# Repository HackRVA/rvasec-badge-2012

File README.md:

RvaSec Badge 2012
=================

This repository contains all the notes, design files and documentation for the RvaSec security conference for 2012

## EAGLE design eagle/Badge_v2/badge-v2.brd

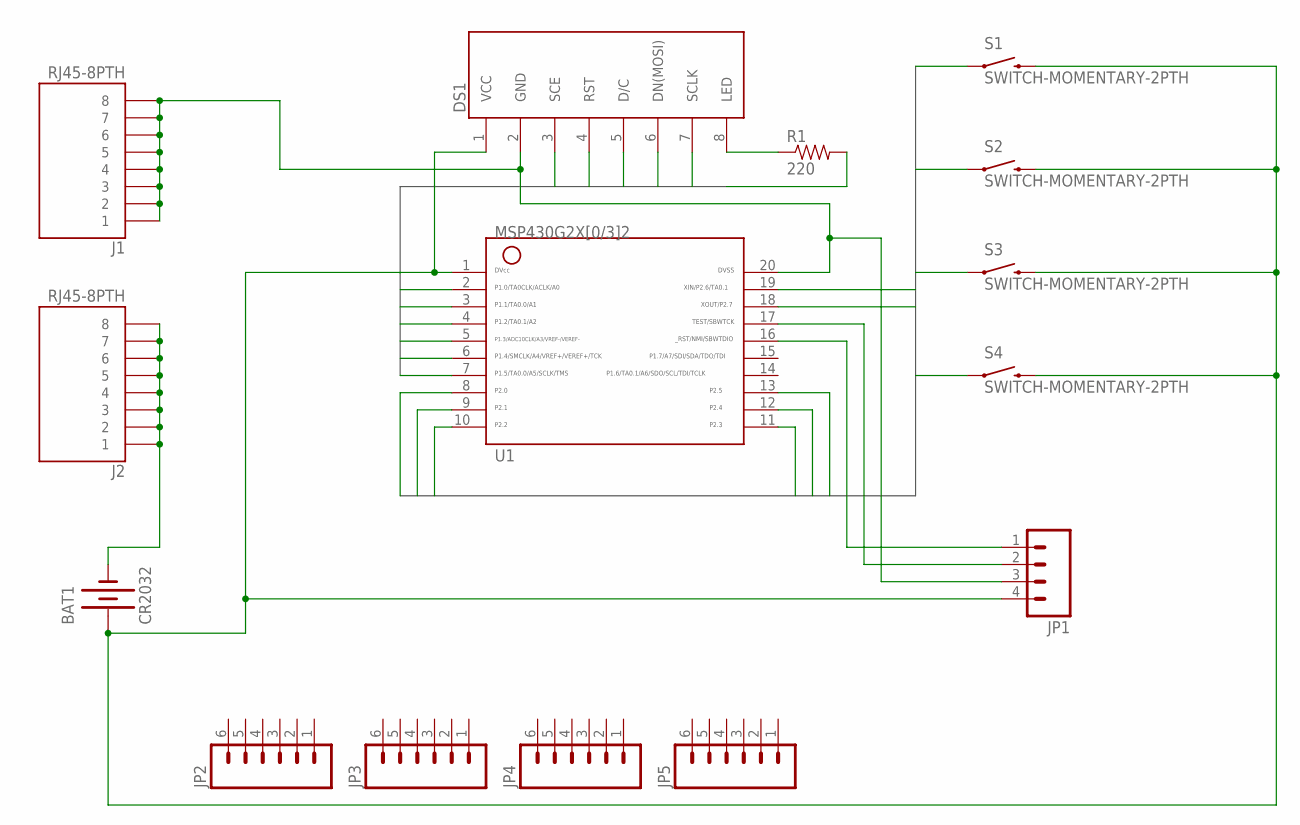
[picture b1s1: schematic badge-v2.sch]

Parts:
BAT1: CR2032; BATTCOM_20MM_4LEGS_PTH
DS1: NOK_5110_LCD; 1X08
J1, J2: RJ45-8PTH; RJ45-8
JP1: M04PTH; 1X04
JP2, JP3, JP4, JP5: M06SIP; 1X06
R1: 220; AXIAL-0.3
S1, S2, S3, S4: SWITCH-MOMENTARY-2PTH; TACTILE-PTH
U1: G2X[0/3]2---N20; N20

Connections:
unnamed: DS1.8 (LED), R1.P$1 (1)
PORTONE0: DS1.4 (RST), U1.2
PORTONE1: DS1.5 (D/C), U1.3
PORTONE2: DS1.6 (DN(MOSI)), U1.4
PORTONE3: DS1.7 (SCLK), U1.5
PORTONE4: R1.P$2 (2), U1.6
PORTONE5: DS1.3 (SCE), U1.7
PORTTWO0: S1.1, U1.8
PORTTWO1: S2.1, U1.9
PORTTWO2: S3.1, U1.10
PORTTWO3: S4.1, U1.11
PORTTWO4: U1.12
PORTTWO5: U1.13
PORTTWO6: U1.19
PORTTWO7: U1.18
RST: JP1.1, U1.16
TEST: JP1.2, U1.17
VCC: BAT1.P$POS1 (+), DS1.1 (VCC), JP1.4, S1.3 (2), S2.3 (2), S3.3 (2), S4.3 (2), U1.1
VSS1: BAT1.P$NEG (-), J2.1, J2.2, J2.3, J2.4, J2.5, J2.6, J2.7, J2.8
VSS2: DS1.2 (GND), J1.1, J1.2, J1.3, J1.4, J1.5, J1.6, J1.7, J1.8, JP1.3, U1.20

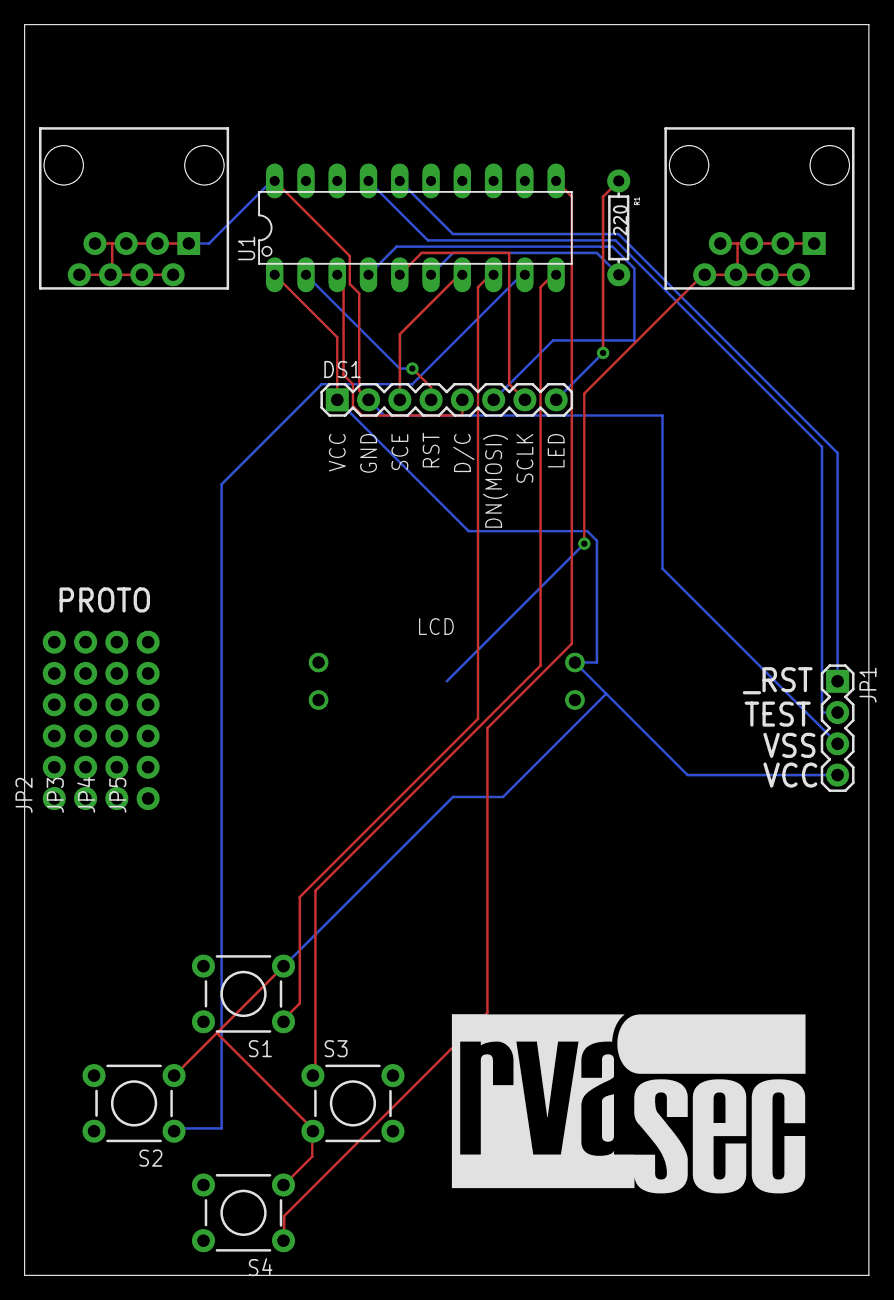
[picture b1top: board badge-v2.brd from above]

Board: 2 copper layers, 68.6 x 101.6 mm, 16 parts (1 on the bottom side), 16 nets.

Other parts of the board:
U$1: RVA_SEC_LOGO_LARGE

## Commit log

2012-05-01 Added initial documentation and readme
    * Added lcd datasheet
    * Added all files to replicate my eagle session
2012-05-01 Project layout changes
    * Added empty eagle project directory
    * Moved files for setting up eagle environment to eagle/env
2012-05-02 Added graphics in various formats
    * Converted graphic to data array compatible with Nokia 5510
2012-05-02 Added MSP430 part library
    * Added schematic file with microcontroller
2012-05-03 Added rough logo display sketch
2012-05-03 Updated image and graphics data array
    * Removed wasted space around edge of image
    * Removed original eagle part libary for MSP430 (renamed)
2012-05-05 Added a second image
    * Modified pins to map to arduino pro mini
2012-06-15 Graphics!
    * Added all final graphics
2012-06-15 Documentation
    Added pdf for rj45 connector
2012-06-15 Added final eagle files
    * NOTE - I have modified some parts from the standard sparkfun library, I
    don't remember all of which. Be warned of my unorganized nature.
2012-06-15 Added custom parts
    * Added the library of parts that weren't in the sparkfun library or
    elsewhere
2012-06-15 Added source files
    * Don't peek at all the goodies before the conference you dirty cheaters
2012-06-16 Added kludgy fix to string compare
2012-06-16 Made it so images don't time out
2012-06-16 Added securabit logo

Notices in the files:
parts and their libraries:
SparkFun: Licensing: CC v3.0 Share-Alike You are welcome to use this library for commercial purposes.
